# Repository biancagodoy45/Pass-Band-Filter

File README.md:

Second Homework for Electronics Course. UBB 02-2018

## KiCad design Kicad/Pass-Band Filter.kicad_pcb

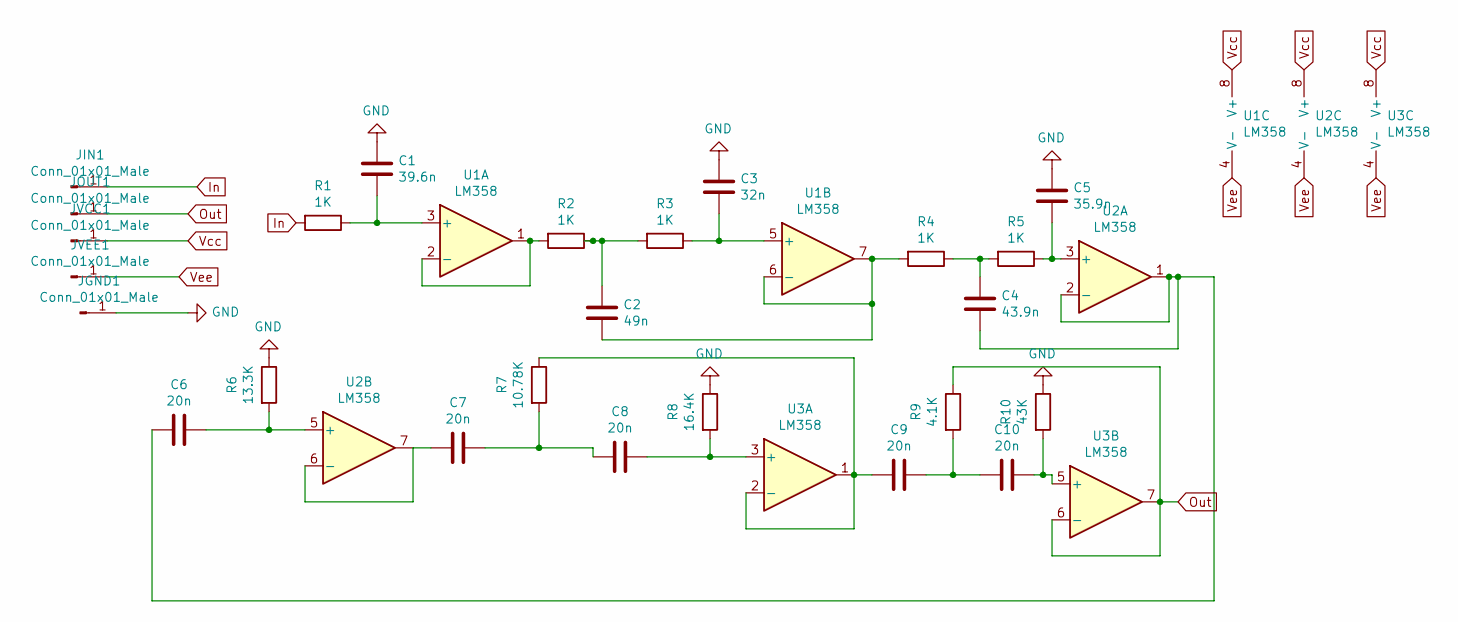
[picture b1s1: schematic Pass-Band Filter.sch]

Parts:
C1: 39.6n; C_0603_1608Metric_Pad1.05x0.95mm_HandSolder
C2: 49n; C_0603_1608Metric_Pad1.05x0.95mm_HandSolder
C3: 32n; C_0603_1608Metric_Pad1.05x0.95mm_HandSolder
C4: 43.9n; C_0603_1608Metric_Pad1.05x0.95mm_HandSolder
C5: 35.9n; C_0603_1608Metric_Pad1.05x0.95mm_HandSolder
C6, C7, C8, C9, C10: 20n; C_0603_1608Metric_Pad1.05x0.95mm_HandSolder
JGND1: Conn_01x01_Male; PinHeader_1x01_P1.00mm_Vertical
JIN1: Conn_01x01_Male; PinHeader_1x01_P1.00mm_Vertical
JOUT1: Conn_01x01_Male; PinHeader_1x01_P1.00mm_Vertical
JVCC1: Conn_01x01_Male; PinHeader_1x01_P1.00mm_Vertical
JVEE1: Conn_01x01_Male; PinHeader_1x01_P1.00mm_Vertical
R1, R2, R3, R4, R5: 1K; R_1206_3216Metric
R6: 13.3K; R_1206_3216Metric
R7: 10.78K; R_1206_3216Metric
R8: 16.4K; R_1206_3216Metric
R9: 4.1K; R_1206_3216Metric
R10: 43K; R_1206_3216Metric
U1, U2, U3: LM358; DIP-8_W7.62mm_Socket_LongPads

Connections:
GND: C1.1, C3.1, C5.1, JGND1.1, R6.1, R8.1, R10.1
In: JIN1.1, R1.2
unnamed: C1.2, R1.1, U1.3 (+)
unnamed: C2.1, R2.1, R3.2
unnamed: C2.2, R4.2, U1.6 (-), U1.7
unnamed: C3.2, R3.1, U1.5 (+)
unnamed: C4.1, R4.1, R5.2
unnamed: C4.2, C6.2, U2.1, U2.2 (-)
unnamed: C5.2, R5.1, U2.3 (+)
unnamed: C6.1, R6.2, U2.5 (+)
unnamed: C7.1, C8.2, R7.2
unnamed: C7.2, U2.6 (-), U2.7
unnamed: C8.1, R8.2, U3.3 (+)
unnamed: C9.2, R7.1, U3.1, U3.2 (-)
unnamed: C10.1, R10.2, U3.5 (+)
unnamed: C9.1, C10.2, R9.2
unnamed: R2.2, U1.1, U1.2 (-)
Out: JOUT1.1, R9.1, U3.6 (-), U3.7
Vcc: JVCC1.1, U1.8 (V+), U2.8 (V+), U3.8 (V+)
Vee: JVEE1.1, U1.4 (V-), U2.4 (V-), U3.4 (V-)

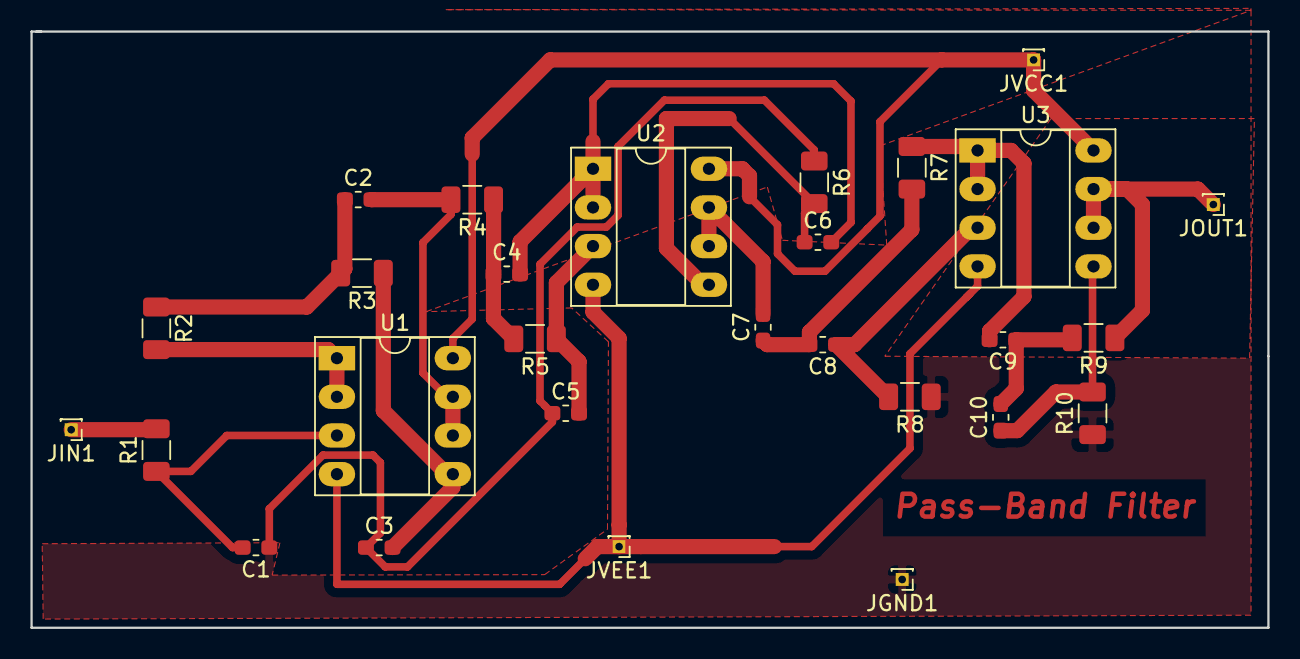
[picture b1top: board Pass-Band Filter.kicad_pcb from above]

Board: 2 copper layers, 81.3 x 39.2 mm, 28 parts (0 on the bottom side), 20 nets.
